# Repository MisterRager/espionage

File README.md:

# espionage
SPI breakout board for the ESP8266

This is my first attempt at making a PCB layout. It's called "espionage" because it's for getting the SPI bus on the ESP8266.

I'm not particularly familiar with open-source hardware licenses, but please use anything you find useful here. Just let me know if you want to try to make money off of my work even if you don't intend to give me any of that money.

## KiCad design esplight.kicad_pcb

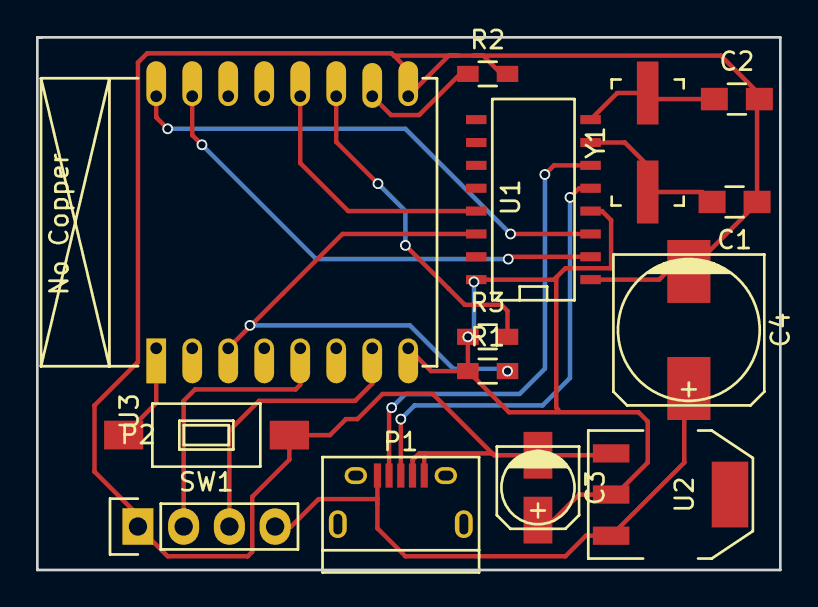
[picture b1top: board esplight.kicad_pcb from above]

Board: 2 copper layers, 41.3 x 29.6 mm, 14 parts (0 on the bottom side), 16 nets.

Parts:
C1, C2: 22pF; C_0805_HandSoldering
C3: 22uF; c_elec_4x5.8
C4: 470uF; c_elec_8x10
P1: USB_B; USB_Micro-B
P2: CONN_01X04; Socket_Strip_Straight_1x04
R1, R2, R3: 10kE; R_0603_HandSoldering
SW1: SW_PUSH; SW_SPST_FSMSM
U1: CH340G; SO-16-N
U2: AMS1117; SOT-223
U3: ESP-07v2
Y1: 20MHz; Crystal_CSM-3X_SMD

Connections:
/3.3V: C3.1, R1.1, R3.1, U1.4, U1.16, U2.2, U3.8
/5V: C4.1, P1.1, P2.4, U2.3
/CLOCK: P2.2, U3.5
/DTR: U1.13, U3.12
/GND: C1.1, C2.2, C3.2, C4.2, P1.4, P1.5, P2.1, R2.2, SW1.1, U1.1, U2.1, U3.9
/MOSI: P2.3, U3.7
/RESET: SW1.2, U3.1
/RTS: R1.2, U1.14, U3.3
/RX: U1.3, U3.16
/TX: U1.2, U3.15
unnamed: C1.2, U1.7, Y1.1
unnamed: C2.1, U1.8, Y1.2
unnamed: P1.2, U1.6
unnamed: P1.3, U1.5
unnamed: R2.1, U3.10
unnamed: R3.2, U3.11

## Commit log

2015-11-19 Initial commit - creating esplight repo for project
2015-11-21 got the board to a more or less finished state - gonna try variants now
2015-11-21 added script for bundling stuff up to print at oshpark
2015-12-30 connecting chip_en pin, fixing some resistors
2016-01-05 Version 2 of the board - added USB/TTL and more SMT
2016-01-05 forgot new footprint
2016-01-05 added exclusion zone under the antenna
